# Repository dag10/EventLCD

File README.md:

EventLCD
========

A project using an Arduino Ethernet and LCD character display to show upcoming events in a location from a shared Google calendar.

Pictures and more info can be found on [my blog](http://drewgottlieb.net/2014/03/02/opensource-event-display.html).

Details
-------

### Hardware

The hardware consists of:
 - Arduino Ethernet w/ a POE (Power Over Ethernet) module [Amazon Link](http://www.amazon.com/gp/product/B005D22FR6/ref=oh_details_o03_s00_i00)
 - 20x4 Amerlight LCD Module with HD44780 controller [Amazon Link](http://www.amazon.com/gp/product/B00D7Z2BWU/ref=oh_details_o09_s00_i01)
 - Custom PCB for connecting the Arduino with the LCD module (see /pcb)
   - 74LS595 Shift register
   - 10K Trim potentiometer
   - 16-pin header row
 - Generic project enclosure
 - POE Injector

### Software

 - Flask-powered web server that pulls the events from Google Calendar and renders a 20x4 character HTTP response containing what the LCD should display. (see /website)
   - Configurable items: Google API token, Google Calendar ID
 - C++ Arduino code. (see /arduino)
   - Configurable items: MAC address

Hardware Instructions
--------

1. Drill out your enclosure to expose the LCD screen and Arduino's ethernet port.
2. Solder shift register and trimpot onto custom PCB.
3. Solder wires to pads on custom PCB.
4. Solder custom PCB onto back of LCD module with header pins.
5. Attach (perhaps with hot glue) the LCD module and Arduino into the enclosure.
6. Plug those wires onto the Arduino's pins. Look at the Arduino code for pin mapping.
7. Install the software (see below), and you're done! Just plug it into powered ethernet.

Software Instructions
--------

### Arduino sketch

I'm using [ino](http://inotool.org) to build the arduino code. If you use ino, you must delete the Robot_Control library from your Arduino IDE installation ([explanation here](https://github.com/amperka/ino/issues/85)).

To use ino, navigate to the arduino directory and run `ino build` then `ino upload`. If you build using the Arduino IDE, make sure to add the libraries in the lib folder.

### Web application

Go to the website directory and run setup.sh to install the virtualenv with flask and its extensions. Then copy app.yaml.example to app.yaml and insert your Google API token and Google calendar ID.

To run the app, execute `./run.py`.

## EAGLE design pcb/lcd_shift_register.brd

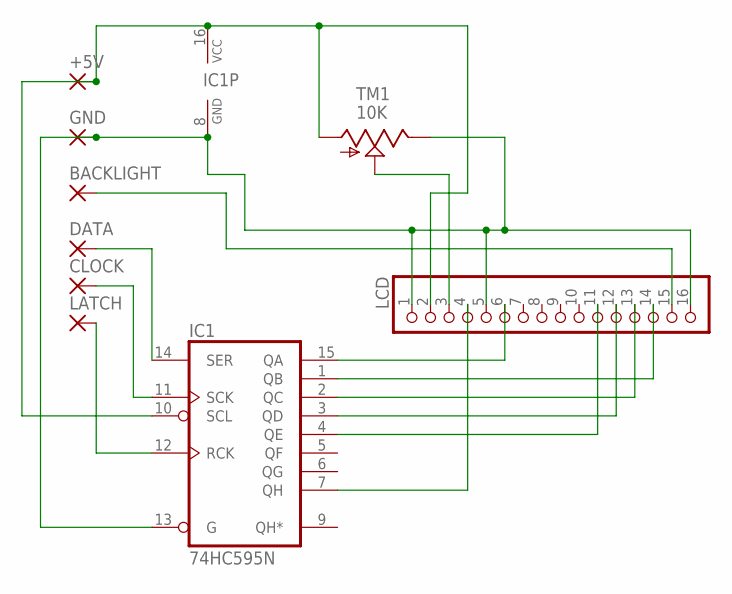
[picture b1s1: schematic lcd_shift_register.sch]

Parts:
+5V: 2,15/1,0
BACKLIGHT: 2,15/1,0
CLOCK: 2,15/1,0
DATA: 2,15/1,0
GND: 2,15/1,0
IC1: 74HC595N; DIL16
LATCH: 2,15/1,0
LCD: PINHD-1X16; 1X16
TM1: 10K; 6MM

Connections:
unnamed: +5V.1, IC1.10 (SCL), IC1.16 (VCC), LCD.2, TM1.A
unnamed: GND.1, IC1.8 (GND), IC1.13 (G), LCD.1, LCD.5, LCD.16, TM1.E
unnamed: BACKLIGHT.1, LCD.15
unnamed: LCD.3, TM1.S
unnamed: DATA.1, IC1.14 (SER)
unnamed: IC1.12 (RCK), LATCH.1
unnamed: CLOCK.1, IC1.11 (SCK)
unnamed: IC1.1 (QB), LCD.14
unnamed: IC1.2 (QC), LCD.13
unnamed: IC1.3 (QD), LCD.12
unnamed: IC1.4 (QE), LCD.11
unnamed: IC1.15 (QA), LCD.6
unnamed: IC1.7 (QH), LCD.4

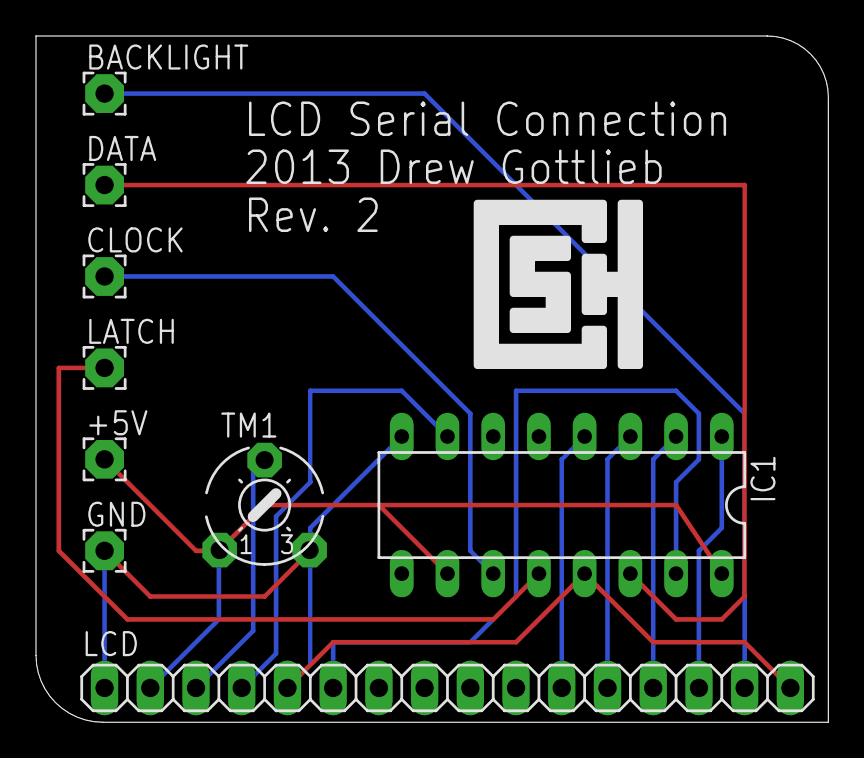
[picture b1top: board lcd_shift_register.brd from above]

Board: 2 copper layers, 44.0 x 38.1 mm, 9 parts (0 on the bottom side), 13 nets.

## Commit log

2013-10-16 Started code files, created backlight controller.
2013-10-16 Created display controller with basic network status screen. Connects to ethernet, but doesn't manage to display if connected or not.
2013-10-16 Added simple build notes for arduino sketch.
2013-10-16 Update display on loop, and improve network screen.
2013-10-16 Backlight can now pulse a certain amount of times, and can have a delay.
    Additional code refactoring.
2013-10-16 Added flask to start webpage.
2013-10-16 Added flask website files with URL route to retrieve upcoming events in JSON format.
2013-10-16 Added port and host to config, and added 'requests' to setup.
2013-10-16 Added web build instructions to readme.
2013-10-20 Added Request class; sketch downloads body of web page.
2013-10-21 Arduino fetches plain-text web page and displays it once.
2013-10-21 Restructured sketch program flow to handle issues well.
    Backlight flashes on errors.
    Moved move things to settings, such as room name and url.
2013-10-21 Website now renders out content for LCD to display.
2013-10-22 Client disconnects on error.
    Refresh rate changed to 20 seconds.
2013-10-22 Current events shown with a 'NOW: ' in front.
2013-10-22 Filter out all-day events.
2013-10-23 Fixed Arduino.h includes.
2013-10-23 Fixed url char allocation to maybe fix crash problem. Also only updates screen during request if screen is network.
    Also added subtle pulsing to backlight as a heartbeat.
2013-10-23 Presence of a [lcd: <value>] tag overrides display event.
    'No more events today' won't be shown if error is being displayed.
    Newlines stripped from error messages.
2013-10-27 Added PCB schematics of rev2.
    This is the version sent off to OSHPark for the first batch.
2013-10-27 Sets brightness to first line of HTTP response.
    Also slowed down backlight fade speed.
2014-01-27 Server sends low brightness during nighttime.
2014-02-16 Setup.sh explicitly uses python2.7 now.
2014-03-02 Added more details and instructions to README.me.
    Mostly copied from internal CSH wiki.
2014-04-06 Center 'no more events' message, and only show if events = 0.
2014-04-06 Wrap Flask with Tornado for hopefully improved stability.
2014-07-06 Added blog post link to README.md.
2016-02-14 Add a startup script for EventLCD
